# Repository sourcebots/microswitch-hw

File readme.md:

# Microswitch PCB

As part of the Smallpeice summer school, students create sensors to mount on their robots. Previously, this has been done using breadboards and veroboard. This suffered from issues with fitting the microswitch pins into the breadboards and mounting the board to the robot.

As such, this PCB is designed to be a simple breakout board for a microswitch. It has footprints for a microswitch, debouncing circuitry and a 3-pin screw terminal to connect to the board. The board is designed to be mounted on 2020 aluminium extrusion chassis with M5 screws.

## Components
- [Right-angle microswitch](https://www.lcsc.com/product-detail/C504864.html): C504864
- [Screw terminal block](https://www.lcsc.com/product-detail/C5188435.html): C5188435

## Resources

- [Schematic PDF](https://sourcebots.github.io/microswitch-hw/Schematic/switch_pcb-schematic.pdf)
- [Interactive BOM](https://sourcebots.github.io/microswitch-hw/Assembly/switch_pcb-ibom.html)
- [BOM CSV](https://sourcebots.github.io/microswitch-hw/BoM/Generic/switch_pcb-bom.csv)
- [Gerbers (JLCPCB format)](https://sourcebots.github.io/microswitch-hw/Manufacturers/switch_pcb-_JLCPCB_compress.zip)
- [3D model (STEP)](https://sourcebots.github.io/microswitch-hw/3D/switch_pcb-3D.step)
- [Assembly drawings](https://sourcebots.github.io/microswitch-hw/PCB/PDF/switch_pcb-assembly.pdf)

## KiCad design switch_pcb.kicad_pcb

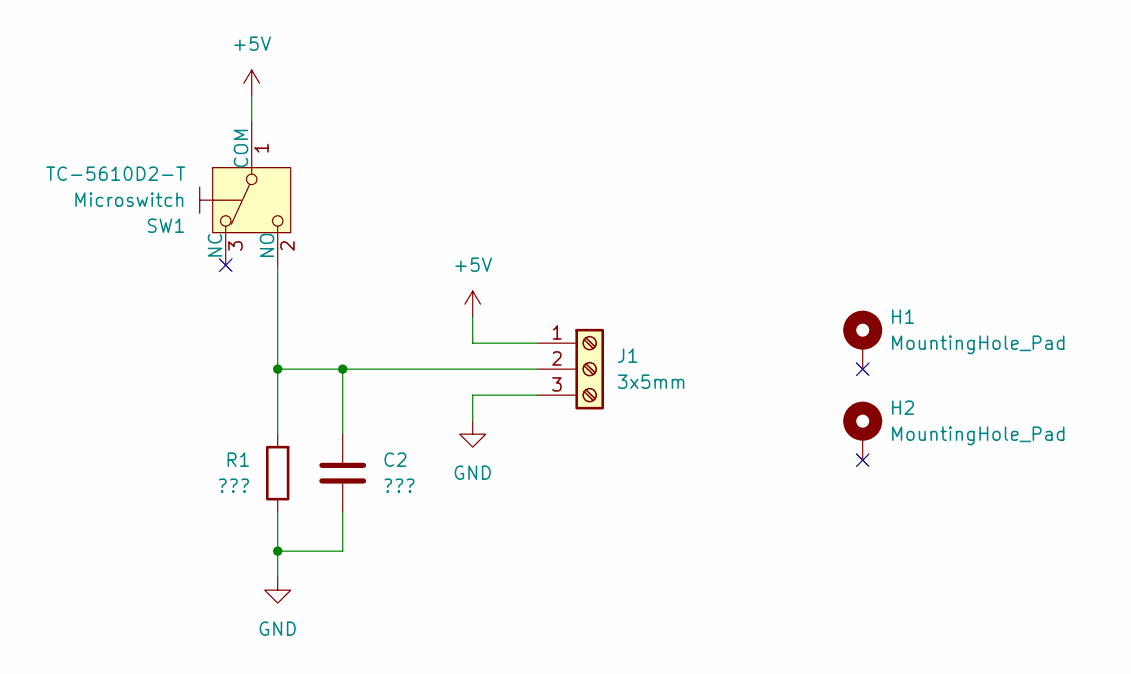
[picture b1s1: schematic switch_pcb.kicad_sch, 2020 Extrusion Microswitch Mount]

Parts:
C2: ???; C_Disc_D9.0mm_W5.0mm_P5.00mm
H1, H2: MountingHole_Pad; MountingHole_5.3mm_M5_ISO7380_Pad
J1: 3x5mm; TerminalBlock_Phoenix_MKDS-1,5-3_1x03_P5.00mm_Horizontal; JLC C5188435
R1: ???; R_Axial_DIN0207_L6.3mm_D2.5mm_P10.16mm_Horizontal
SW1: Microswitch; TC-5610D2-T; JLC C504864

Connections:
+5V: J1.1, SW1.1 (COM)
GND: C2.2, J1.3, R1.1
unnamed: C2.1, J1.2, R1.2, SW1.2 (NO)

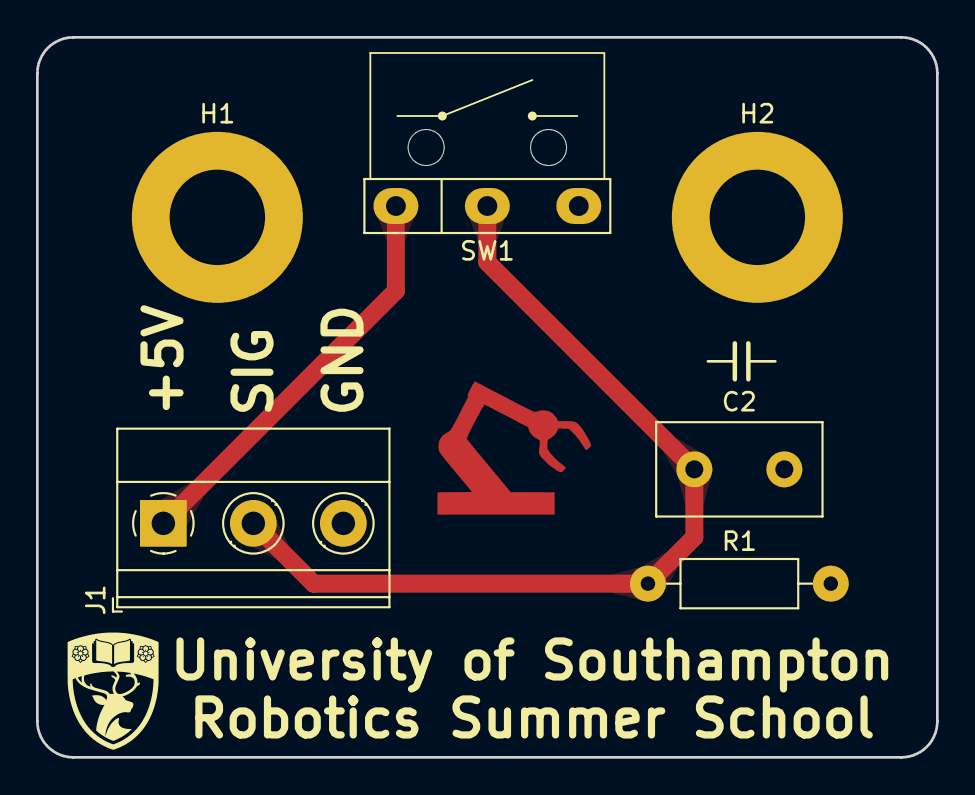
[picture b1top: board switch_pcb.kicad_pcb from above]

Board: 2 copper layers, 50.0 x 40.0 mm, 6 parts (0 on the bottom side), 3 nets.

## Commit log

2024-05-13 Base schematic
2024-05-13 Add some footprints and mounting holes
2024-05-14 Switch to only breaking out the normally open circuit
2024-06-17 Create footprints
2024-06-17 Setup PCB DRC
2024-06-17 Rough first layout
2024-06-17 Add rough 3D model for switch
2024-06-18 Reworked layout
2024-06-18 Improve silkscreen, add SRO logo
2024-06-19 Try a quick CI
2024-06-19 Switch to ENIG
2024-06-19 Try and put outputs on github pages
2024-06-19 Retry upload to pages
2024-06-23 Make SRO arm fill copper Not just soldermask
2024-06-23 Extend PCB, add course name and logo, add initial area on PCB
2024-06-23 Review feedback Center PCB on page Remove 5V plane & use teardrops Change circuit to be pulled up & switched low
2024-06-24 Improve DRC
2024-06-24 Switch back to the previous circuit with switch at the top
2024-06-29 Add readme
2026-03-22 Update to "UoS Robotics Summer School" Switch to UoS logo Update to Kicad v9
2026-03-22 Upgrade CI to Kicad 9
2026-03-29 Note components used
2026-03-29 Setup for serial number
